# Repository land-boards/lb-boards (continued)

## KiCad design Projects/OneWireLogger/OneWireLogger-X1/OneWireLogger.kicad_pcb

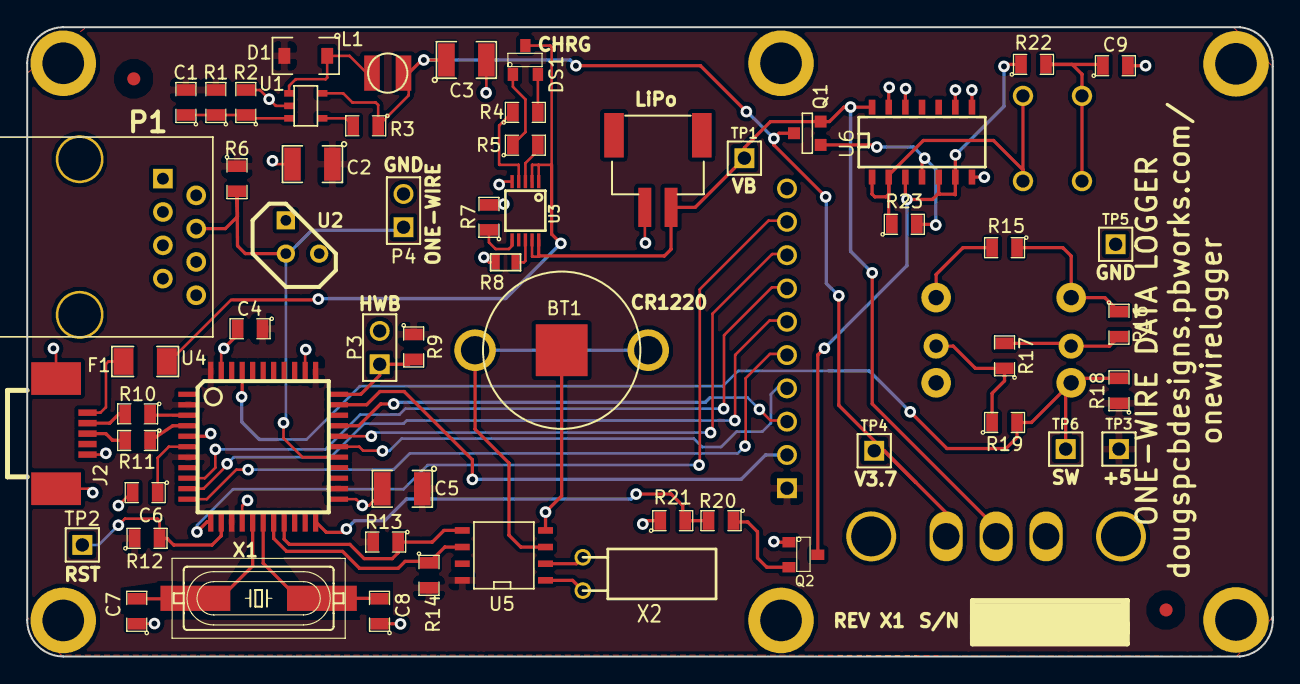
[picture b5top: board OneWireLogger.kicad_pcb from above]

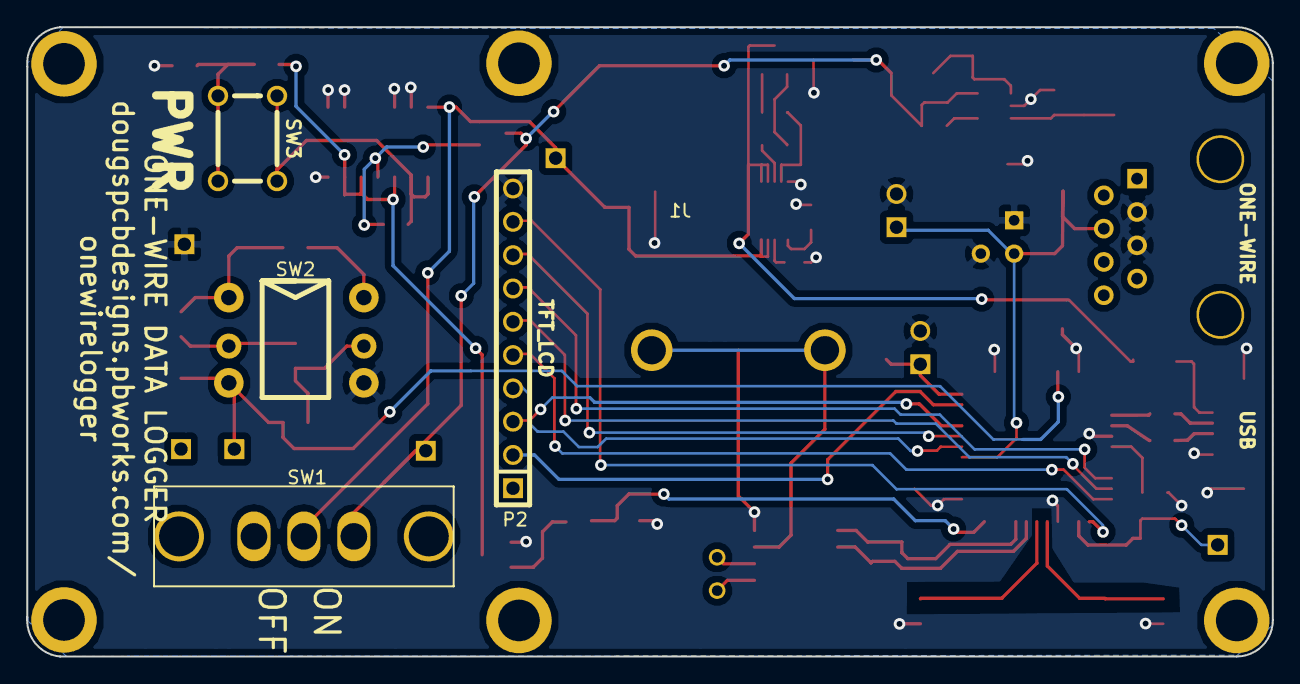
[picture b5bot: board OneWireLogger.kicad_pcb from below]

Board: 2 copper layers, 95.0 x 48.0 mm, 71 parts (4 on the bottom side), 49 nets.

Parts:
BT1: BATTERY; BATTERY_12MM
C1: 680pF; SM0805
C2, C3: 4.7uF; SM1210
C4, C9: 0.1uF; SM0805
C5: 10uF; SM1210
C6: 1uF; SM0805
C7, C8: 18pF; SM0805
D1: MBR0520LT1G; SOD-123
DS1: LED2C_CA; SOT23
F1: FUSE; SM1206
FID1, FID2: CONN_1; FIDUCIAL
J1: JST_2; JST-2-SMT
J2: USB-B; USB-B-MINI
L1: 10uH; IND-3MM
MTG1, MTG2, MTG3, MTG4, MTG5, MTG6: CONN_1; MTG-4-40-SMALL
P1: CNT-RJ45-8; RJ45_8-TH
P2: TFT_LCD; PIN_ARRAY-10X1
P3, P4: CONN_2; PIN_ARRAY_2X1
Q1: DMG3415U-7; SOT23GDS
Q2: 2N3904; SOT23
R1: 3.09K; SM0805
R2, R16, R20: 1K; SM0805
R3: 1M; SM0805
R4, R5: 470; SM0805
R6: 4.7K; SM0805
R7: 2.2K; SM0805
R8: NTC-10K; SM0603
R9, R12, R13, R14, R21: 10K; SM0805
R10, R11: 22; SM0805
R15: 3.3K; SM0805
R17: 560; SM0805
R18: 1.8K; SM0805
R19: 330; SM0805
R22, R23: 100K; SM0805
REV_BLOCK1: REV_BLOCK
SW1: SW-SPDT; SW-SPDT-SLIDE
SW2: SW5WAY
SW3: SW_PUSH_OMRON; SW-PB-6MM
TP1, TP2, TP3, TP4, TP5, TP6: TST; PIN_ARRAY_1
U1: LMR62014; SOT23-5
U2: DS18S20+; TO92
U3: MCP73833; MSOP10-0.5
U4: ATMEGA32U4-AU; TQFP44
U5: DS1307; SO8N
U6: MC14093; SO14E
X1: CRYSTAL; crystal-HC49UP
X2: 32.768KHz; QMONTRE

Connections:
+5V: C1.2, C2.1, C4.1, C5.1, D1.2, P2.1, R1.2, R6.1, R9.1, R12.1, R13.2, R14.2, R18.1, TP3.1, U4.2, U4.7, U4.14, U4.24, U4.34, U4.44, U5.8
/5-Way Switch/SW5WAY: R18.2, R19.2, SW2.3, TP6.1, U4.41
/5V Power Supply/3.7V: C3.1, L1.1, Q1.D, R3.1, SW1.1, TP4.1, U1.5
/LiPo Battery Charger/VB-3.7: J1.2, Q1.S, SW1.2, TP1.1, U3.9, U3.10, U6.14
/Microprocessor/BKLT: P2.2, U4.32
/Microprocessor/BUSBP: R11.1, U4.4
/Microprocessor/BUSPM: R10.1, U4.3
/Microprocessor/LCDCS: P2.8, U4.29
/Microprocessor/LCDRS: P2.4, U4.28
/Microprocessor/LCDRST: P2.3, U4.30
/Microprocessor/MISO: P2.5, U4.11
/Microprocessor/MOSI: P2.6, U4.10
/Microprocessor/ONE-WIRE: P1.4, P4.1, R6.2, U2.2, U4.27
/Microprocessor/PWR-OFF: R20.2, R21.2, U4.22
/Microprocessor/RST: R12.2, TP2.1, U4.13
/Microprocessor/SCK: P2.7, U4.9
/Microprocessor/SCLK: R14.1, U4.18, U5.6
/Microprocessor/SDA: R13.1, U4.19, U5.5
/Microprocessor/SDCS: P2.9, U4.12
/Microprocessor/USB5V: F1.2, J2.1
/Microprocessor/USB-DM: J2.2, R10.2
/Microprocessor/USB-DP: J2.3, R11.2
/Microprocessor/V5USB: DS1.3, F1.1, U3.1, U3.2
/Microprocessor/~HWB: P3.1, R9.2, U4.33
/PowerSwitch/GATE: Q1.G, R23.2, U6.4
GND: BT1.2, C2.2, C3.2, C4.2, C5.2, C6.2, C7.1, C8.1, C9.2, J1.1, J2.4, J2.G1, J2.G2, P1.3, P1.5, P2.10, P3.2, P4.2, Q2.1, R2.2, R7.2, R8.2, R21.1, SW2.4, TP5.1, U1.2, U2.1, U2.3, U3.5, U4.5, U4.15, U4.23, U4.35, U4.43, U5.4, U6.7, U6.8, U6.9, U6.12, U6.13
unnamed: R7.1, U3.6
unnamed: R8.1, U3.8
unnamed: DS1.1, R5.1
unnamed: R4.1, U3.4
unnamed: DS1.2, R4.2
unnamed: R5.2, U3.3
unnamed: C1.1, R1.1, R2.1, U1.3
unnamed: D1.1, L1.2, U1.1
unnamed: R3.2, U1.4
unnamed: C8.2, U4.17, X1.2
unnamed: C6.1, U4.6
unnamed: C7.2, U4.16, X1.1
unnamed: BT1.1, U5.3
unnamed: U5.1, X2.1
unnamed: U5.2, X2.2
unnamed: R17.1, R19.1, SW2.5
unnamed: R15.2, SW2.6
unnamed: R16.2, R17.2, SW2.2
unnamed: R15.1, R16.1, SW2.1
unnamed: Q2.2, R20.1
unnamed: C9.1, R22.2, SW3.1, SW3.2
unnamed: R23.1, SW3.3, SW3.4, U6.1, U6.2
unnamed: Q2.3, R22.1, U6.3, U6.5, U6.6

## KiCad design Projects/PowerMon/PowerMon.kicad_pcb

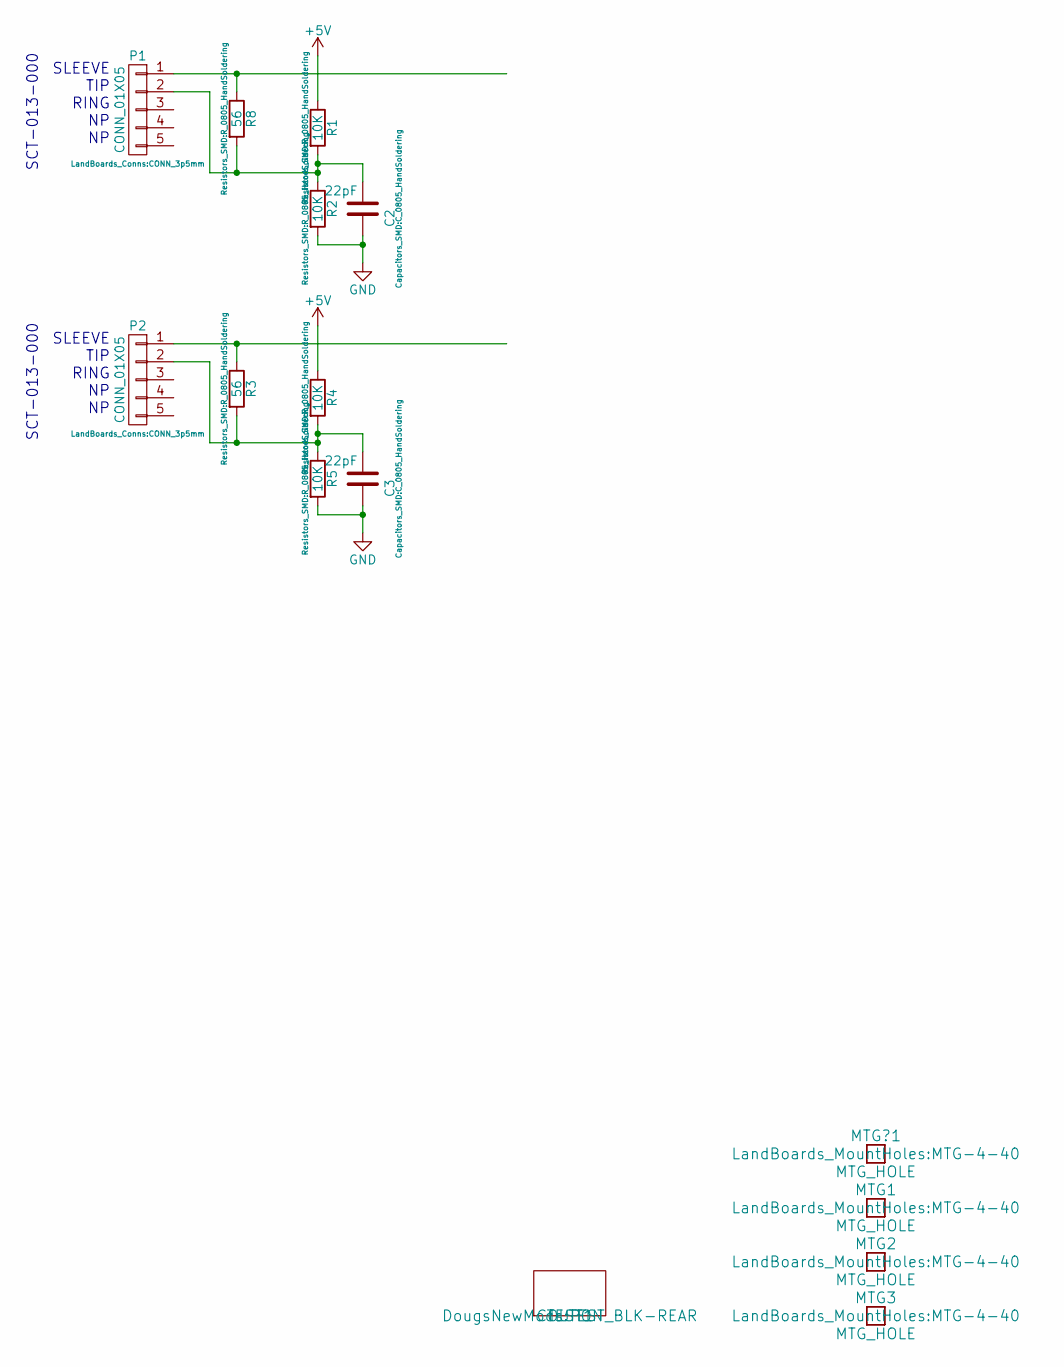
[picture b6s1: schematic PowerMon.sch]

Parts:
C2, C3: 22pF; C_0805_HandSoldering
MTG1, MTG2, MTG3: MTG_HOLE; MTG-4-40
MTG?1: MTG_HOLE; MTG-4-40
P1, P2: CONN_01X05; CONN_3p5mm
R1, R2, R4, R5: 10K; R_0805_HandSoldering
R3, R8: 56; R_0805_HandSoldering
TEST1: COUPON; TEST_BLK-REAR

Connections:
+5V: R1.1, R4.1
GND: C2.1, C3.1, R2.2, R5.2
unnamed: C2.2, P1.2, R1.2, R2.1, R8.2
unnamed: C3.2, P2.2, R3.2, R4.2, R5.1
unnamed: P1.1, R8.1
unnamed: P2.1, R3.1

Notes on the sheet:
SLEEVE TIP RING NP NP
SCT-013-000

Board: 2 copper layers, 14 parts (0 on the bottom side), 6 nets, no tracks yet.

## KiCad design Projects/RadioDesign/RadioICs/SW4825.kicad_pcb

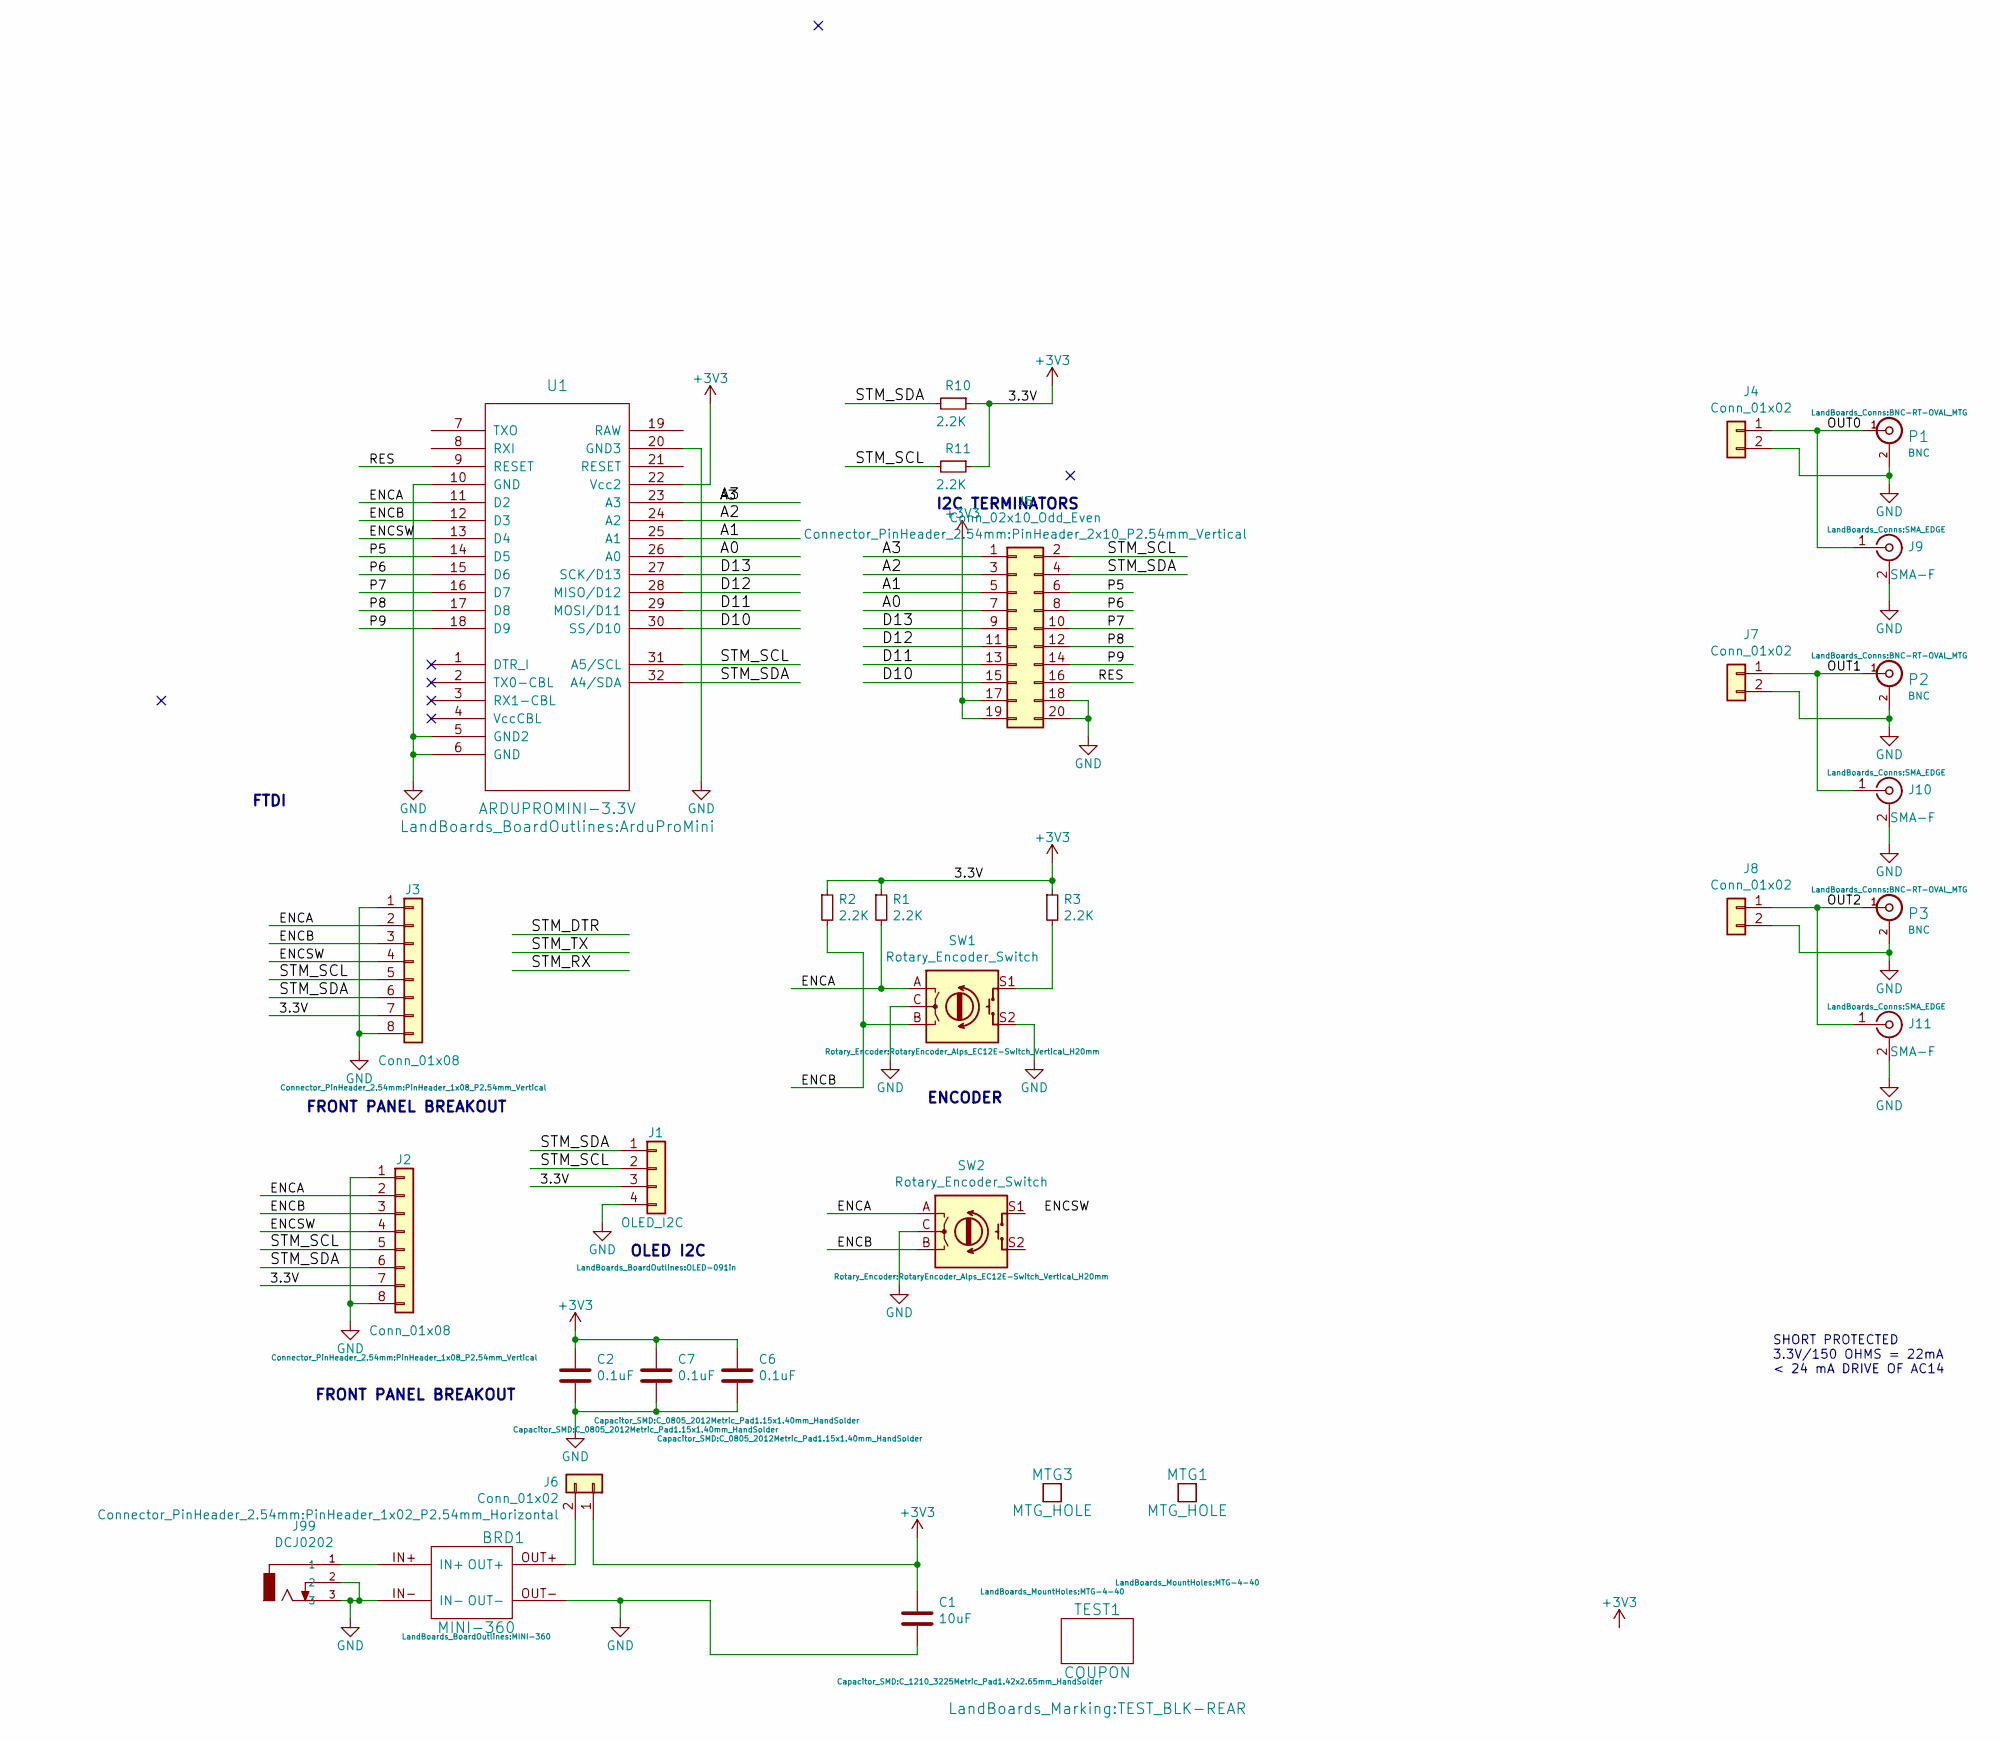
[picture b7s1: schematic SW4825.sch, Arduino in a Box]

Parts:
BRD1: MINI-360
C1: 10uF; C_1210_3225Metric_Pad1.42x2.65mm_HandSolder
C2, C6, C7: 0.1uF; C_0805_2012Metric_Pad1.15x1.40mm_HandSolder
J1: OLED_I2C; OLED-091in
J2, J3: Conn_01x08; PinHeader_1x08_P2.54mm_Vertical
J4, J7, J8: Conn_01x02; PinHeader_1x02_P2.54mm_Vertical
J5: Conn_02x10_Odd_Even; PinHeader_2x10_P2.54mm_Vertical
J6: Conn_01x02; PinHeader_1x02_P2.54mm_Horizontal
J9, J10, J11: SMA-F; SMA_EDGE
J99: DCJ0202; DCJ-NEW-Slotted
MTG1, MTG3: MTG_HOLE; MTG-4-40
P1, P2, P3: BNC; BNC-RT-OVAL_MTG
R1, R2, R3, R10, R11: 2.2K; R_0805_2012Metric_Pad1.15x1.40mm_HandSolder
SW1, SW2: Rotary_Encoder_Switch; RotaryEncoder_Alps_EC12E-Switch_Vertical_H20mm
TEST1: COUPON; TEST_BLK-REAR
U1: ARDUPROMINI-3.3V; ArduProMini

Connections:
+3V3: C1.1, C2.1, C6.1, C7.1, J1.3, J2.7, J3.7, J5.17, J5.19, J6.1, R1.1, R2.1, R3.1, R10.1, R11.1, U1.22 (Vcc2)
/A0: J5.7, U1.26 (A0)
/A1: J5.5, U1.25 (A1)
/A2: J5.3, U1.24 (A2)
/A3: J5.1, U1.23 (A3)
/D10: J5.15, U1.30 (SS/D10)
/D11: J5.13, U1.29 (MOSI/D11)
/D12: J5.11, U1.28 (MISO/D12)
/D13: J5.9, U1.27 (SCK/D13)
/ENCA: J2.2, J3.2, R1.2, SW1.A, SW2.A, U1.11 (D2)
/ENCB: J2.3, J3.3, R2.2, SW1.B, SW2.B, U1.12 (D3)
/ENCSW: J2.4, J3.4, U1.13 (D4)
/OUT0: J4.1, J9.1 (In), P1.1 (In)
/OUT1: J7.1, J10.1 (In), P2.1 (In)
/OUT2: J8.1, J11.1 (In), P3.1 (In)
/P5: J5.6, U1.14 (D5)
/P6: J5.8, U1.15 (D6)
/P7: J5.10, U1.16 (D7)
/P8: J5.12, U1.17 (D8)
/P9: J5.14, U1.18 (D9)
/RES: J5.16, U1.9 (RESET)
/STM_SCL: J1.2, J2.5, J3.5, J5.2, R11.2, U1.31 (A5/SCL)
/STM_SDA: J1.1, J2.6, J3.6, J5.4, R10.2, U1.32 (A4/SDA)
GND: BRD1.IN-, BRD1.OUT-, C1.2, C2.2, C6.2, C7.2, J1.4, J2.1, J2.8, J3.1, J3.8, J4.2, J5.18, J5.20, J7.2, J8.2, J9.2 (Ext), J10.2 (Ext), J11.2 (Ext), J99.2, J99.3, P1.2 (Ext), P2.2 (Ext), P3.2 (Ext), SW1.C, SW1.S2, SW2.C, U1.5 (GND2), U1.6 (GND), U1.10 (GND), U1.20 (GND3)
unnamed: BRD1.IN+, J99.1
unnamed: BRD1.OUT+, J6.2
unnamed: R3.2, SW1.S1

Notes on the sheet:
OLED I2C
FTDI
FRONT PANEL BREAKOUT
ENCODER
SHORT PROTECTED 3.3V/150 OHMS = 22mA < 24 mA DRIVE OF AC14
I2C TERMINATORS

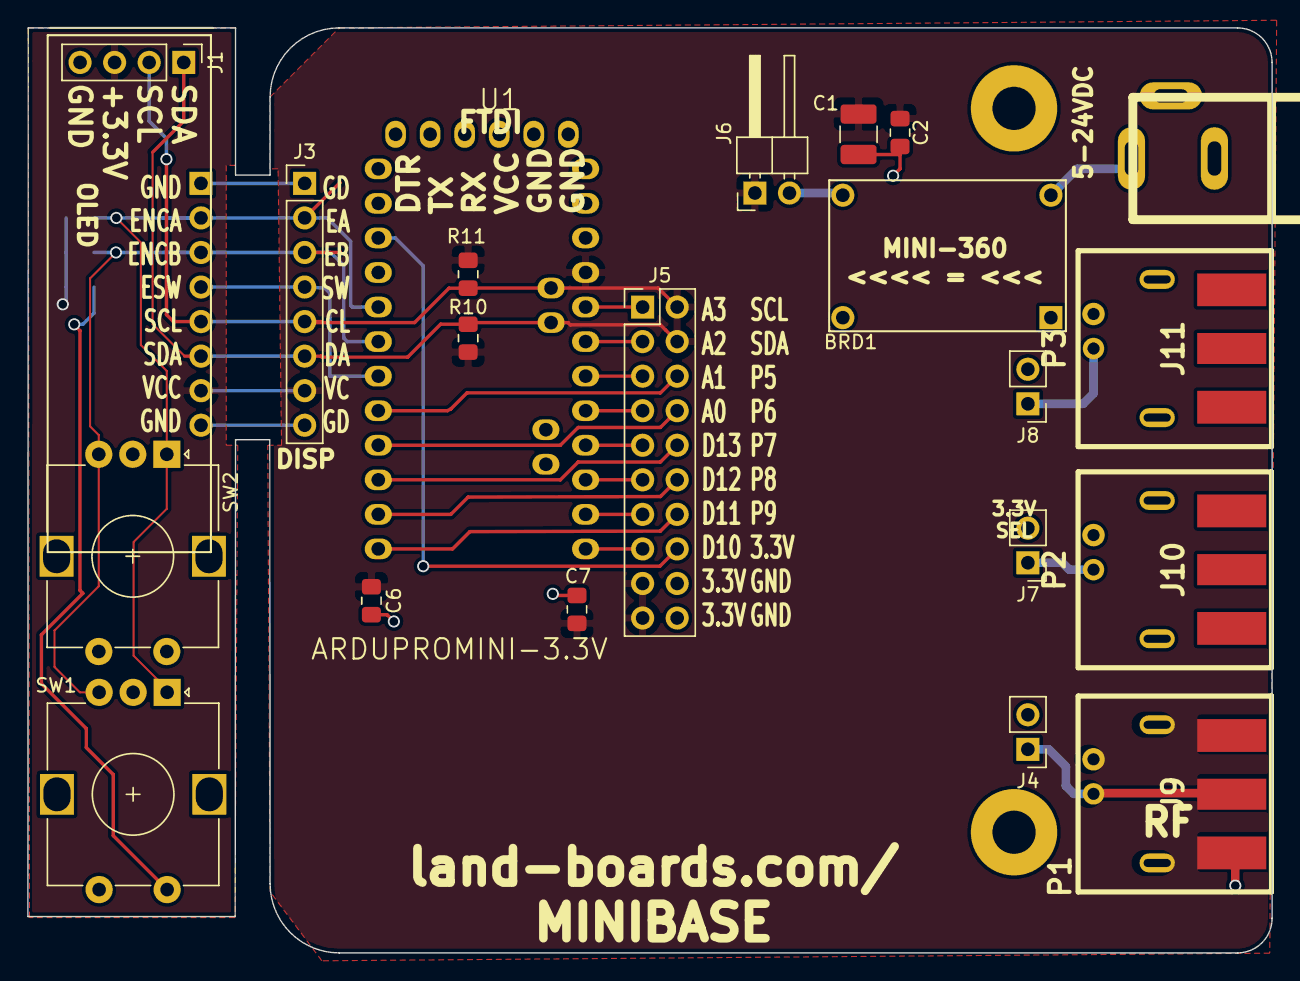
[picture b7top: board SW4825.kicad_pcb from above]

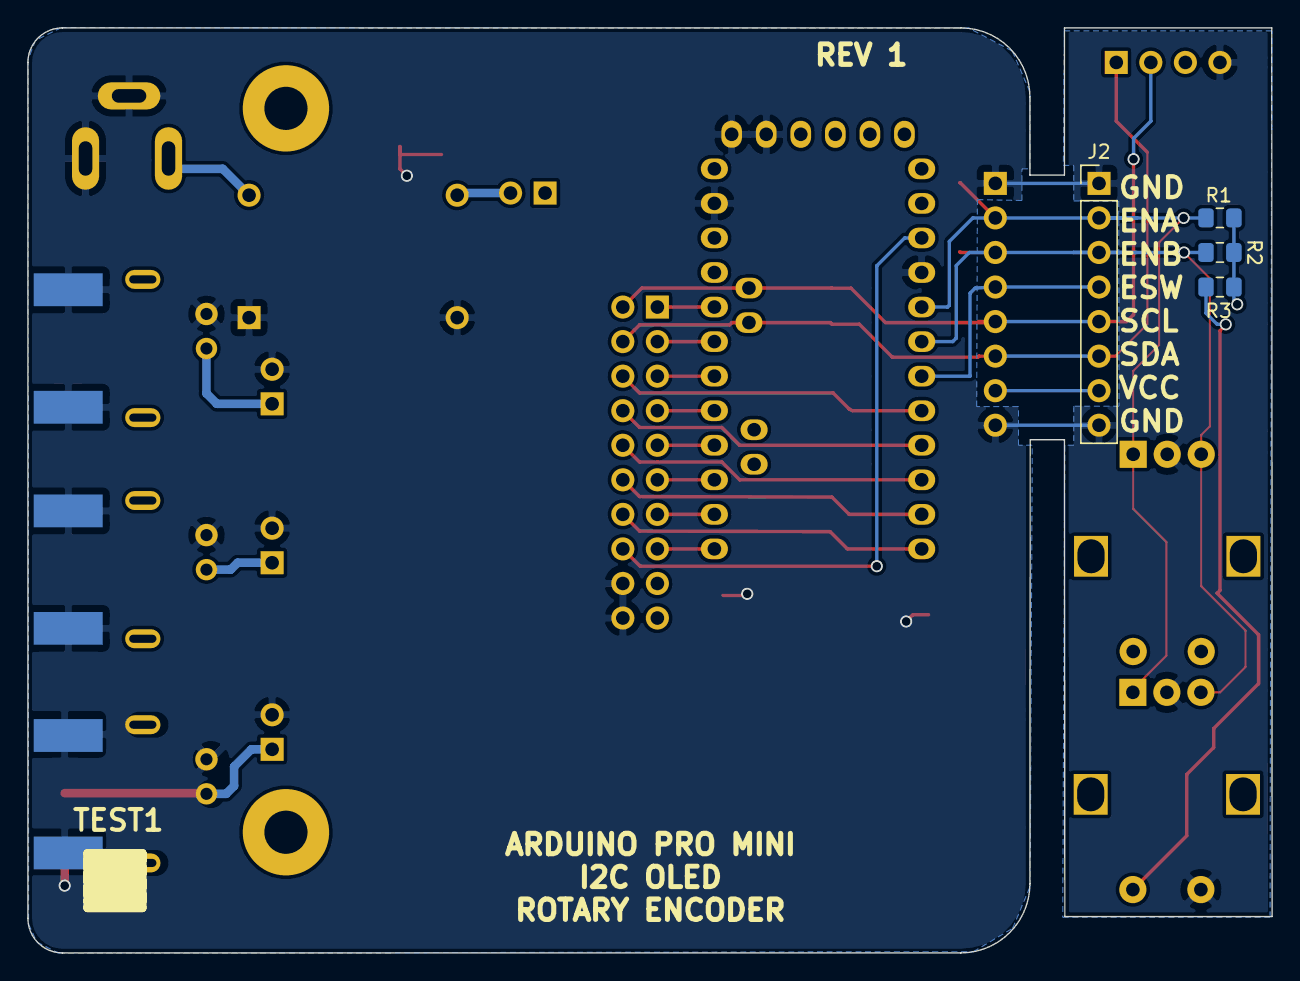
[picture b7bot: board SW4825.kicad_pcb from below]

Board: 2 copper layers, 91.5 x 68.0 mm, 31 parts (4 on the bottom side), 27 nets.
